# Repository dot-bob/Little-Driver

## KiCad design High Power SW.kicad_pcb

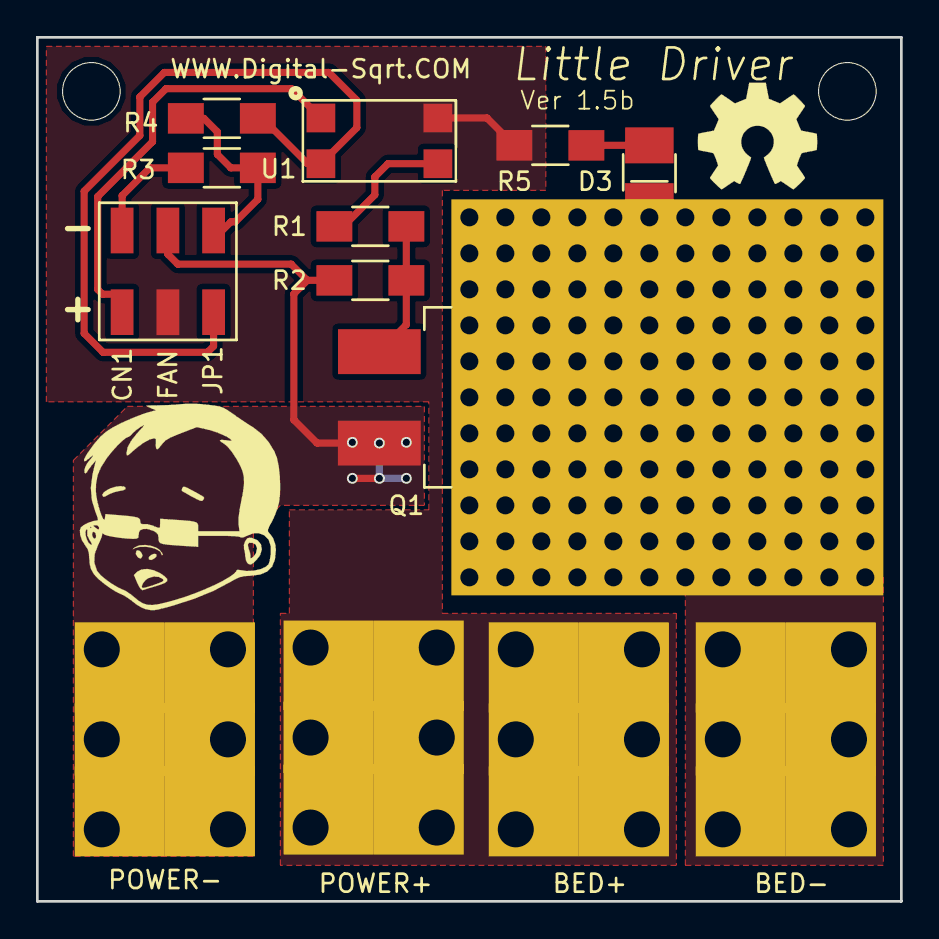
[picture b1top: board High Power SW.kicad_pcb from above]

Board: 2 copper layers, 48.0 x 48.0 mm, 13 parts (0 on the bottom side), 10 nets.

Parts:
BED+: CONN_01X01; Keystone_terminal
BED-: CONN_01X01; Keystone_terminal
CN1: Jumper_NC_Small; 6pin_SMT_HEADER
D3: Led_Small; CREE_CLM1B_AKW_CUAVB253
POWER+: CONN_01X01; Keystone_terminal
POWER-: CONN_01X01; Keystone_terminal
Q1: IRFR7540TRPBF; TO-263-2Lead_(Larg_Heat_Sink_More_Air)
R1: 1.0K; R_1206_HandSoldering
R2: 1.8K; R_1206_HandSoldering
R3: 300; R_1206_HandSoldering
R4: 1.69K; R_1206_HandSoldering
R5: 3.6K; R_1206_HandSoldering
U1: PS2801C-1-A; TLP182

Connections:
+BATT: BED+.1, CN1.3, POWER+.1, R5.1, U1.6
GND: CN1.4, POWER-.1, Q1.3, R2.2
unnamed: BED-.1, D3.1, Q1.4
unnamed: CN1.1, U1.1
unnamed: CN1.2, R3.1
unnamed: D3.2, R5.2
unnamed: CN1.5, R4.2, U1.3
unnamed: CN1.6, R3.2, R4.1
unnamed: Q1.1, R1.2, R2.1
unnamed: R1.1, U1.4

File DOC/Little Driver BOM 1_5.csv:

Reference,Populate,Value,Count,Manufacturer Part No,Manufacturer,Supplyer,Supplyer_Part_No,Datasheet,Supplyer_LinkR4,Yes,1.69K,1,RC1206FR-071K69L,Yageo,Digi-Key,311-1.69KFRCT-ND,http://www.yageo.com/NewPortal/yageodocoutput?fileName=/pdf/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,http://www.digikey.com/product-detail/en/yageo/RC1206FR-071K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POWER+;BED+;BED-;POWER-,Yes,CONN_01X01,4,8197,Keystone Electronics,Digi-Key,36-8197-ND,http://www.keyelco.com/product-pdf.cfm?p=1534,http://www.digikey.com/product-search/en?keywords=36-8197-ndR3,Yes,300,1,RC1206JR-07300RL,Yageo,Digi-Key,311-300ERCT-ND,http://www.yageo.com/NewPortal/yageodocoutput?fileName=/pdf/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,http://www.digikey.com/product-detail/en/yageo/RC1206JR-0730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U1,Yes,PS2801C-1-A,1,PS2801C-1-A,CEL,Digi-Key,PS2801C-1-A-ND,http://www.digikey.com/product-search/en?keywords=PS2801C-1-A,http://www.digikey.com/product-search/en?keywords=PS2801C-1-AR1,Yes,1.0K,1,RC1206FR-071KL,Yageo,Digi-Key,311-1.00KFRCT-ND,http://www.yageo.com/NewPortal/yageodocoutput?fileName=/pdf/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,http://www.digikey.com/product-detail/en/yageo/RC1206FR-071K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D3,Yes,Led_Small,1,CLM1B-AKW-CUAVB253,CREE,Digi-Key,CLM1B-AKW-CUAVB253CT-ND,http://www.cree.com/~/media/Files/Cree/LED%20Components%20an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,http://www.digikey.com/product-search/en?keywords=CLM1B-AKW-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CN1,Yes,Jumper_NC_Small,2,95278-801A06LF,Amphenol FCI,Digi-Key,609-5161-1-ND,http://portal.fciconnect.com/Comergent//fci/drawing/95278.pdf,http://www.digikey.com/product-detail/en/amphenol-fci/67997-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JP1,NO,Jumper_NC_Small,1,969102-0000-DA,3M,Digi-Key,3M9580-ND,http://multimedia.3m.com/mws/media/548120O/3mtm-shunt-ts2186.pdf,http://www.digikey.com/product-detail/en/3m/969102-0000-DA/3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R2;R5,Yes,1.8K,2,RC1206FR-071K8L,Yageo,Digi-Key,311-1.80KFRCT-ND,http://www.yageo.com/NewPortal/yageodocoutput?fileName=/pdf/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,http://www.digikey.com/product-detail/en/yageo/RC1206FR-0724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Q1,Yes,FDD9407_F085,1,FDD9407_F085,Fairchild Semiconductor,Digi-Key,FDD9407_F085CT-ND,https://www.fairchildsemi.com/datasheets/FD/FDD9407_F085.pdf,http://www.digikey.com/product-detail/en/fairchild-semicondu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,,,,,,,,,,,,,,,,,,,,,,,,,,,,,,,,,,,,

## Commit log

2017-02-13 Update Documents
2017-02-15 Updates to user manuals
    Finished the user manuals
2017-02-15 Update Documentation
2017-02-15 Updated BOM
2017-02-15 Added 3d Printed Brackets
2017-02-15 Added BOM pdf
2017-02-16 Update documentation
    Added stuff for wars sizing
2017-02-16 Fixed doc issues
2017-04-02 Clean up Folder
2017-04-28 Update Driver based on feedback
2017-05-14 Update to LIB
2017-06-24 Fix error's in uploded files
    Fix error's in uploded files, for some reason we uploded and old ver.
    This has been corrected
2017-06-24 Update Board to have new input opto
    Gerber files are not built yet
2017-06-25 Improve Manufacture cost
    Reduced the number of holes, Moved parts, Upgraded silk
